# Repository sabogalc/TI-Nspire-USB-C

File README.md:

# TI-Nspire USB-C

This mod draws heavily from [lightcreations's TI-84 USB-C mod](https://github.com/lightcreations/ti84-usbc). I basically took their work and spent 20 minutes editing the footprint for compatibility with the Nspire.

As I outlined in both of my previous NSpire USB-C mods (links [here](https://redd.it/v52uuu) and [here](https://imgur.com/a/yA0KBce)), the pinout on the NSpire is different than on the TI-84, so the mod needs to be done slightly differently.

I swapped the relevant pins on the PCB to match the NSpire's footprint, and I also added a silkscreen label to differentiate this version from the TI-84 version. Below are front and back screenshots of the PCB.

While this board should work in theory, the left side of it will be extremely close to the LED indicator, as seen below.

This may make it necessary to make a slimmer version 2 of this board, but we'll cross that bridge when we get there. For now it should work as is, and I'll update this repository with any information once I've got the boards in.

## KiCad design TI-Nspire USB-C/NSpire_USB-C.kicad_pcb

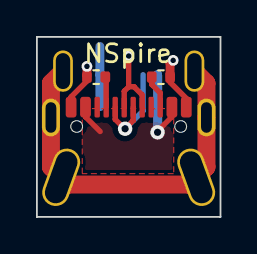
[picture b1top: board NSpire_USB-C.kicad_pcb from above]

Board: 2 copper layers, 10.2 x 10.0 mm, 4 parts (1 on the bottom side), 7 nets.

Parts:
J1: USB_OTG; ti84_mini_usb
J2: USB_C_Receptacle_USB2.0; usb4105
R1, R2: 5.1k; R_0402_1005Metric

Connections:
/D+: J1.3 (D+), J2.A6 (D+), J2.B6 (D+)
/D-: J1.2 (D-), J2.A7 (D-), J2.B7 (D-)
/SHIELD: J1.6 (Shield), J2.S1 (SHIELD)
/VBUS: J1.1 (VBUS), J2.A4 (VBUS), J2.B4 (VBUS), J2.B9 (VBUS)
GND: J1.5 (GND), J2.A12 (GND), J2.B12 (GND), R1.2, R2.2
unnamed: J2.A5 (CC1), R1.1
unnamed: J2.B5 (CC2), R2.1
